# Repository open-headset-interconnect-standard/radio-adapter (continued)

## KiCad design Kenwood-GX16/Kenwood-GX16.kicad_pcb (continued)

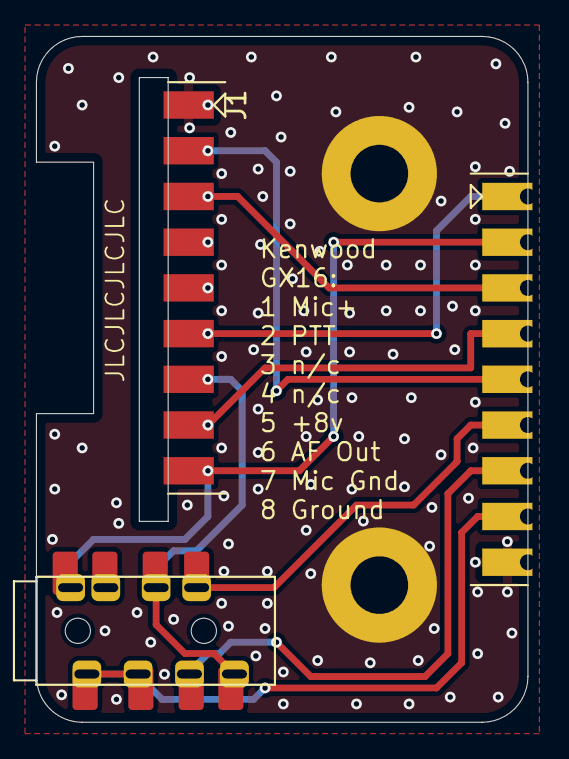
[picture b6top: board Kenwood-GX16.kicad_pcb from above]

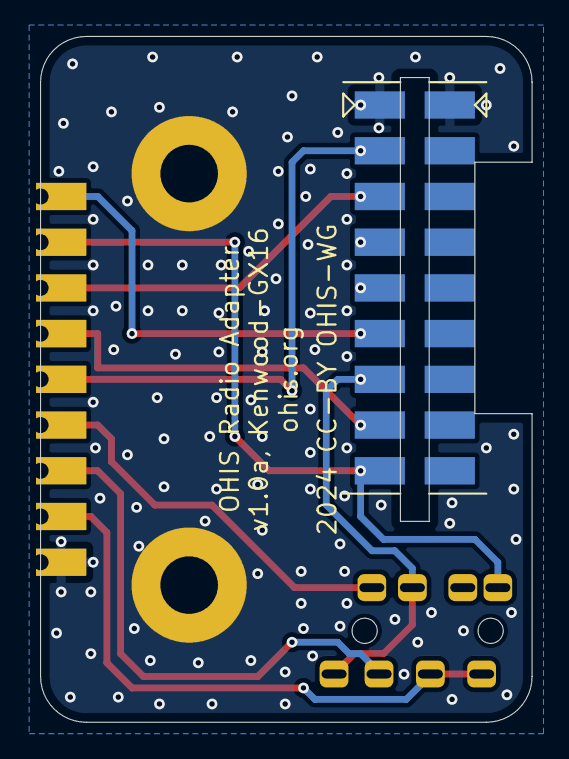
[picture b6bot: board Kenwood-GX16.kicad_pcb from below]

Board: 2 copper layers, 27.3 x 38.1 mm, 7 parts (2 on the bottom side), 12 nets.

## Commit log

2024-04-04 Initial commit of license, and goals in readme.
2024-04-04 Document directory structure. #1
2024-04-05 Initial swag at a very simple Icom radio adapter. #1
2024-04-05 Adding a Yaesu example. #1
2024-04-05 Icom pinout references. Renamed Earth to Shield.
2024-04-05 Yaesu mic pinout references. #1
2024-04-05 Simple Kenwood Radio Adapter. #1
2024-04-05 A bit of documentation for Icom/ Yaesu/ Kenwood/ #1
2024-04-05 Testing Webhooks. #1
2024-04-16 Printing schematics to PDFs.
2024-04-18 See #1, for Icom. Not happy with this, but committing for record.
2024-04-18 Ignoring fabrication toolkit output files.
2024-04-19 For #1. Looks much more like the User Adapter.
2024-04-22 Kenwood laid out more similarly to the User Adapter. #1
2024-04-22 Moving to common BaseBoard architecture. #1
2024-04-24 Happy with BaseBoard and Icom-RJ45. Working on Icom-GX16 #1
2024-04-24 Icom-GX16 added. Also GX16 riser board. #1
2024-04-24 Splitting Yaesu/ out into three directories: RJ45, GX16, 6p6c #1
2024-04-24 Yaesu and Kenwood radio boards. #1 As ordered prototypes v1.0a
2024-07-17 Ordered hardware, sending hardware to @gx1400 for testing.
2024-12-03 I can't find 1.6mm washers/spacers ANYWHERE. So I make my own. #1
2024-12-03 Updated BOM parts, among other things. Sorry, it's been a while. #1
2024-12-03 Added parts list, and current status, to README.md #1
2025-04-29 Added an Interactive BOM for the Base Board assembly.
2025-04-29 Moving iBOM
2025-04-29 Making iBOM available through github Pages
2025-05-28 Radio Adapter v2. Active, isolated. RF protection. As ordered 2025-05-29
2025-05-28 radio adapter v2 front and back panels.
